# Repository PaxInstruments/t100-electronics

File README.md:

# t100-electronics

### Overview
Pax Instruments T100 thermocouple USB adapter.

## T100 Projects

- [Electronics](https://github.com/PaxInstruments/t100-electronics)
- [Enclosure](https://github.com/PaxInstruments/t100-enclosure)
- [Firmware](https://github.com/PaxInstruments/t100-firmware)
- [Software](https://github.com/PaxInstruments/t100-software)

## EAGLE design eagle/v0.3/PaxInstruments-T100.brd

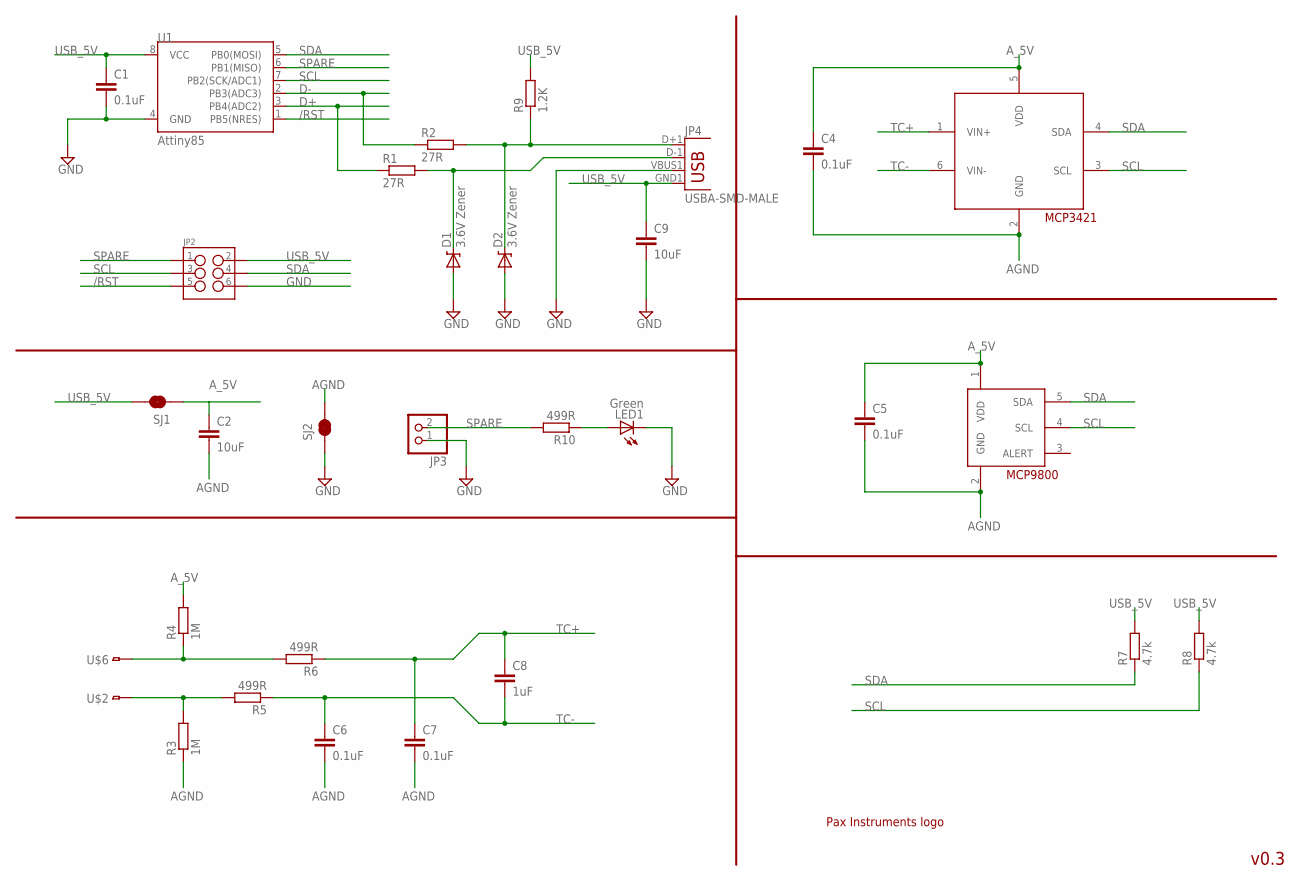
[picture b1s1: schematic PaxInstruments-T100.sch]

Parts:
C1, C4, C5, C6, C7: 0.1uF; C0603; TOLERANCE 5%; MPN CC0603JRX7R9BB104
C2, C9: 10uF; 1206; TOLERANCE 10%; MPN CC1206KKX5R7BB106
C8: 1uF; C0603; TOLERANCE 10%; MPN GRM155R60J105KE19D
D1, D2: 3.6V Zener; SOD-323; MPN BZT52C3V6S-7-F
JP2: M03X2SMT; 2X3_SMT_POSTS; MPN 95278-101A06LF
JP3: HEADER-1X2ROUND; 1X02_ROUND
JP4: USBA-SMD-MALE; USB-A-SMT-MALE
LED1: Green; LED-0603; MPN LTST-C191KGKT
R1, R2: 27R; R0603; TOLERANCE 5%; MPN RC0603JR-0727RL
R3, R4: 1M; R0603; TOLERANCE 1%; MPN RC0603FR-071ML
R5, R6, R10: 499R; R0603; TOLERANCE 0.5%; MPN RT0603DRD07499RL
R7, R8: 4.7k; R0603; TOLERANCE 5%; MPN RC0603JR-074K7L
R9: 1.2K; R0603; TOLERANCE 5%; MPN RC0603JR-071K2L
SJ1, SJ2: JUMPER-PAD-2-NC_BY_TRACENO_SILK; PAD-JUMPER-2-NC_BY_TRACE_NO_SILK
U1: Attiny85; SO08-EIAJ; MPN ATTINY85-20SUR
U$1: PAX-LOGOPAX-LOGO-0.25IN; PAX-LOGO-0.25IN
U$2, U$6: TC-MINI-SINGLE; TC-CLIP-SINGLE; MPN 1024
U$3: MCP3421A0; SOT23-6; MPN MCP3421A0T-E/CH
U$4: MCP9800A0; SOT23-5; MPN MCP9800A0T-M/OT

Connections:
/RST: JP2.5, U1.1 (PB5(NRES))
AGND: C2.2, C4.2, C5.2, C6.2, C7.2, R3.1, SJ2.2, U$3.2 (GND), U$4.2 (GND)
A_5V: C2.1, C4.1, C5.1, R4.2, SJ1.1, U$3.5 (VDD), U$4.1 (VDD)
D+: R1.1, U1.3 (PB4(ADC2))
D-: R2.1, U1.2 (PB3(ADC3))
GND: C1.2, C9.2, D1.2 (A), D2.2 (A), JP2.6, JP3.1, JP4.VBUS1 (VBUS), LED1.C, SJ2.1, U1.4 (GND)
unnamed: D2.1 (C), JP4.D+1 (D+), R2.2, R9.1
unnamed: D1.1 (C), JP4.D-1 (D-), R1.2
unnamed: R3.2, R5.2, U$2.P$1
unnamed: R4.1, R6.2, U$6.P$1
unnamed: LED1.A, R10.1
SCL: JP2.3, R8.1, U1.7 (PB2(SCK/ADC1)), U$3.3 (SCL), U$4.4 (SCL)
SDA: JP2.4, R7.1, U1.5 (PB0(MOSI)), U$3.4 (SDA), U$4.5 (SDA)
SPARE: JP2.1, JP3.2, R10.2, U1.6 (PB1(MISO))
TC+: C7.1, C8.1, R6.1, U$3.1 (VIN+)
TC-: C6.1, C8.2, R5.1, U$3.6 (VIN-)
USB_5V: C1.1, C9.1, JP2.2, JP4.GND1 (GND), R7.2, R8.2, R9.2, SJ1.2, U1.8 (VCC)

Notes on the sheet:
v0.3

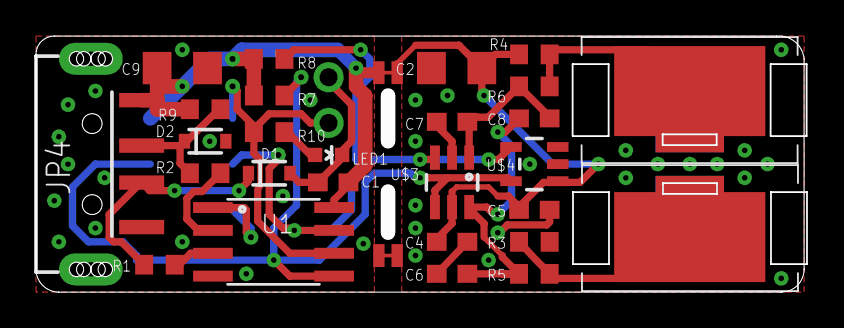
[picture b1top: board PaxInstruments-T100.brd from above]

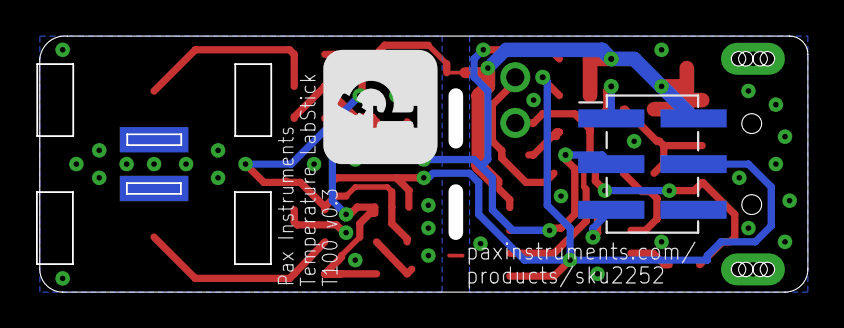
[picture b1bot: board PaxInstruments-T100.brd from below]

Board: 2 copper layers, 42.1 x 13.4 mm, 32 parts (2 on the bottom side), 17 nets.

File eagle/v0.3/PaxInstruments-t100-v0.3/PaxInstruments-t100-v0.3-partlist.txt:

Partlist

Exported from PaxInstruments-T100.sch at 2015-10-05 13:11

EAGLE Version 6.5.0 Copyright (c) 1988-2013 CadSoft

Assembly variant: 

Part     Value          Device                Package        Library                   Sheet

C1       0.1uF          C-EUC0603             C0603          rcl                       1
C2       10uF           CAP1206               1206           SparkFun-Passives         1
C4       0.1uF          C-EUC0603             C0603          rcl                       1
C5       0.1uF          C-EUC0603             C0603          rcl                       1
C6       0.1uF          C-EUC0603             C0603          rcl                       1
C7       0.1uF          C-EUC0603             C0603          rcl                       1
C8       1uF            C-EUC0603             C0603          rcl                       1
C9       10uF           CAP1206               1206           SparkFun-Passives         1
D1       3.6V Zener     DIODE-ZENER-BZT52     SOD-323        SparkFun-DiscreteSemi     1
D2       3.6V Zener     DIODE-ZENER-BZT52     SOD-323        SparkFun-DiscreteSemi     1
JP1      USB-A-H        USB-A-H               USB-A-H        SparkFun-Connectors       1
JP2                     M03X2SMT              2X3_SMT_POSTS  SparkFun-Connectors       1
JP3                     HEADER-1X2ROUND       1X02_ROUND     microbuilder              1
LED1     Green          LED0603               LED-0603       SparkFun-LED              1
R1       27R            R-EU_R0603            R0603          rcl                       1
R2       27R            R-EU_R0603            R0603          rcl                       1
R3       1M             R-EU_R0603            R0603          rcl                       1
R4       1M             R-EU_R0603            R0603          rcl                       1
R5       499R           R-EU_R0603            R0603          rcl                       1
R6       499R           R-EU_R0603            R0603          rcl                       1
R7       4.7k           R-EU_R0603            R0603          rcl                       1
R8       4.7k           R-EU_R0603            R0603          rcl                       1
R9       1.2K           R-EU_R0603            R0603          rcl                       1
R10      499R           R-EU_R0603            R0603          rcl                       1
R11      0R             R-EU_R0603            R0603          rcl                       1
R12      0R             R-EU_R0603            R0603          rcl                       1
U$2      TC-MINI-SINGLE TC-MINI-SINGLE        TC-CLIP-SINGLE PaxInstruments-Connectors 1
U$3      MCP3421A0      MCP3421               SOT23-6        SparkFun-DigitalIC        1
U$4      MCP9800A0      MCP9800               SOT23-5        SparkFun-DigitalIC        1
U$6      TC-MINI-SINGLE TC-MINI-SINGLE        TC-CLIP-SINGLE PaxInstruments-Connectors 1
U1       Attiny85       ATTINY45TINY45-20-SMT SO08-EIAJ      SparkFun-DigitalIC_ihsan  1

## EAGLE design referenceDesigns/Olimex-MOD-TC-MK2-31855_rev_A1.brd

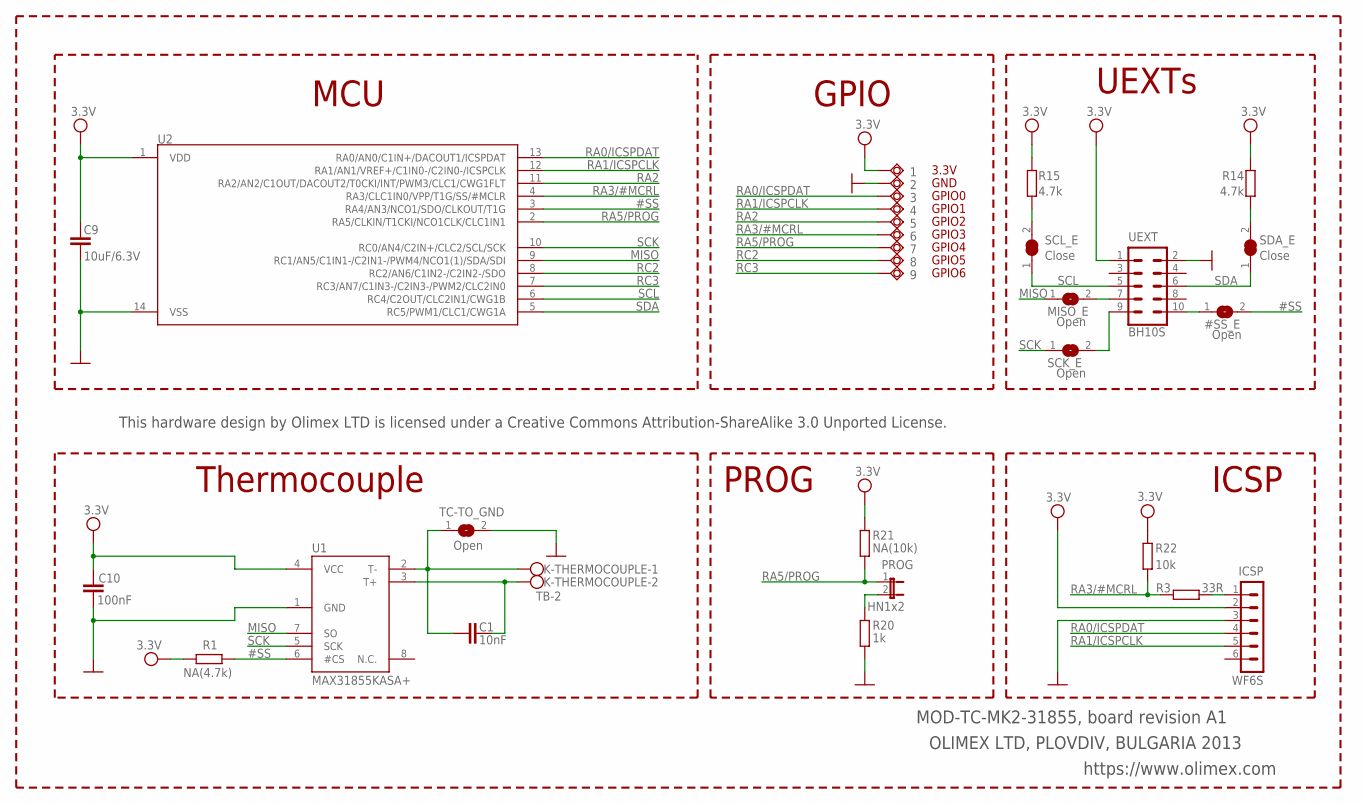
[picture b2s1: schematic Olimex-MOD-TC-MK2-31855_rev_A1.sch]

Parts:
1, 2, 3, 4, 5, 6, 7, 8, 9: TESTPAD40/70; TESTPAD
#SS_E: Open; SJ_1_SMALLER
C1: 10nF; C0603_5MIL
C9: 10uF/6.3V; C0603_5MIL
C10: 100nF; C0603_5MIL
ICSP: WF6S
K-THERMOCOUPLE: TB-2; AK500/2
MISO_E: Open; SJ_1_SMALLER
PROG: HN1x2; JP1
R1: NA(4.7k); R0603_5MIL
R3: 33R; R0603_5MIL
R14, R15: 4.7k; R0603_5MIL
R20: 1k; R0603_5MIL
R21: NA(10k); R0603_5MIL
R22: 10k; R0603_5MIL
SCK_E: Open; SJ_1_SMALLER
SCL_E: Close; SJ_1_SMALLER_CLOSE
SDA_E: Close; SJ_1_SMALLER_CLOSE
TC-TO_GND: Open; SJ_1_SMALLER
U1: MAX31855KASA+; SO-08
U2: PIC16F1503-I/SL; SOIC14
UEXT: BH10S; ML10_PADS

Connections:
#SS: #SS_E.2, R1.2, U1.6 (#CS), U2.3 (RA4/AN3/NCO1/SDO/CLKOUT/T1G)
GND: 2.P$1, C9.2, C10.2, ICSP.3, R20.1, TC-TO_GND.2, U1.1 (GND), U2.14 (VSS), UEXT.2
MISO: MISO_E.1, U1.7 (SO), U2.9 (RC1/AN5/C1IN1-/C2IN1-/PWM4/NCO1(1)/SDA/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)
unnamed: #SS_E.1, UEXT.10
unnamed: SCK_E.2, UEXT.9
unnamed: MISO_E.2, UEXT.7
unnamed: C1.1, K-THERMOCOUPLE.1, TC-TO_GND.1, U1.2 (T-)
unnamed: C1.2, K-THERMOCOUPLE.2, U1.3 (T+)
unnamed: ICSP.1, R3.1
unnamed: R14.1, SDA_E.2
unnamed: R15.1, SCL_E.2
unnamed: PROG.2, R20.2
RA0/ICSPDAT: 3.P$1, ICSP.4, U2.13 (RA0/AN0/C1IN+/DACOUT1/ICSPDAT)
RA1/ICSPCLK: 4.P$1, ICSP.5, U2.12 (RA1/AN1/VREF+/C1IN0-/C2IN0-/ICSPCLK)
RA2: 5.P$1, U2.11 (RA2/AN2/C1OUT/DACOUT2/T0CKI/INT/PWM3/CL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)
RA3/#MCRL: 6.P$1, R3.2, R22.2, U2.4 (RA3/CLC1IN0/VPP/T1G/SS/#MCLR)
RA5/PROG: 7.P$1, PROG.1, R21.1, U2.2 (RA5/CLKIN/T1CKI/NCO1CLK/CLC1IN1)
RC2: 8.P$1, U2.8 (RC2/AN6/C1IN2-/C2IN2-/SDO)
RC3: 9.P$1, U2.7 (RC3/AN7/C1IN3-/C2IN3-/PWM2/CLC2IN0)
SCK: SCK_E.1, U1.5 (SCK), U2.10 (RC0/AN4/C2IN+/CLC2/SCL/SCK)
SCL: SCL_E.1, U2.6 (RC4/C2OUT/CLC2IN1/CWG1B), UEXT.5
SDA: SDA_E.1, U2.5 (RC5/PWM1/CLC1/CWG1A), UEXT.6
VCC: 1.P$1, C9.1, C10.1, ICSP.2, R1.1, R14.2, R15.2, R21.2, R22.1, U1.4 (VCC), U2.1 (VDD), UEXT.1

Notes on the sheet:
ICSP
MCU
UEXTs
Thermocouple
GPIO4
GPIO5
GPIO6
GPIO1
GPIO2
GPIO3
GPIO0
GND
3.3V
GPIO
PROG
MOD-TC-MK2-31855, board revision A1
OLIMEX LTD, PLOVDIV, BULGARIA 2013
https://www.olimex.com
This hardware design by Olimex LTD is licensed under a Creative Commons Attribution-ShareAlike 3.0 Unported License.

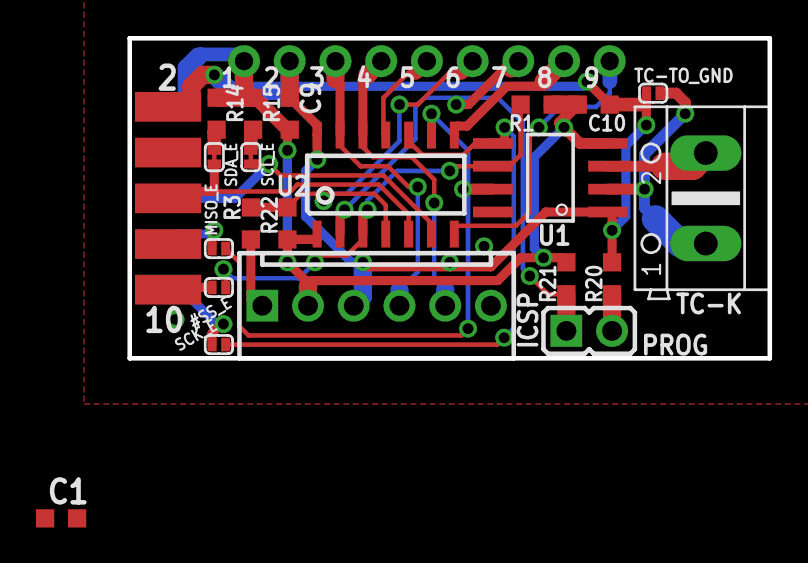
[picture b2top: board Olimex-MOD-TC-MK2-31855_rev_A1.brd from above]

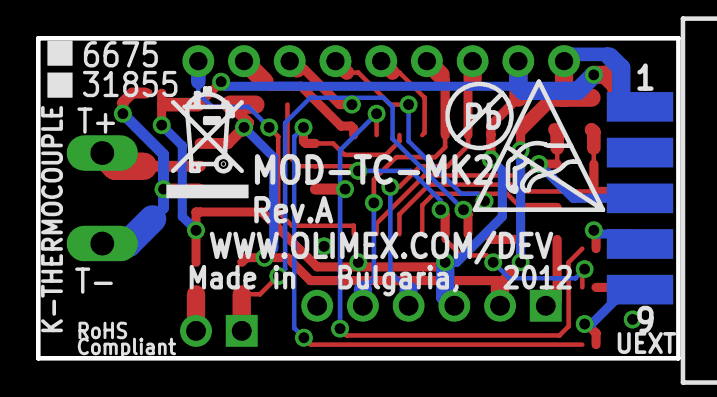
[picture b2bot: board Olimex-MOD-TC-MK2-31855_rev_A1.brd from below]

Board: 2 copper layers, 35.6 x 17.8 mm, 34 parts (4 on the bottom side), 23 nets.

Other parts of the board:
U$1: ESD_SYMBOL
U$6: RECYCLE_BIN1/8
U$7: PB_SMALL

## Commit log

2014-09-16 - added Olimex-MOD-TC-MK2 to referenceDesigns
2014-09-16 - Added SerialCouple to referenceDesigns
2014-09-16 - Added GGLab us tk01 to referenceDesigns
2014-09-16 - Removed spec sheet information. All info is in Github issues
2014-09-21 Initial firmware commit with minimum viable functionality.
2014-09-21 Buffer index fix.
2014-09-22 Firmware is moved to its proper place
2014-10-01 - Added Digispark reference designs - Added USB-to-thermocouple data sheet
2014-10-12 Initial schematic and mockup layout commit.
2014-10-13 ISP connector is modified.
2014-10-13 Layout changes with thermal cutout
2014-10-16 - Changed .gitignore.
2014-11-12 Add fab check files
2014-11-12 Fixed clearance issues, added round corners and version number to the layout
2014-11-28 - Added an order form. This is what Charles uses in China.
2014-11-28 updated .gitignore
    - Ignoring .gpi files
    - Ignoring .dri files
2015-01-01 new file: libraries/PaxInstrument-T400.lbr
2015-01-01 TC connector is updated with the current one. Missing USB pullup resistor added
2015-01-01 modified: libraries/SparkFun-DigitalIC.lbr modified: libraries/charlespax.lbr
2015-01-01 Date code and version number updated
2015-01-02 - Added dottiest
2015-02-23 Initial v0.3 design with isothermal plane connection changed to solder jumper.
2015-02-23 Added indicator LED and breakout header.
2015-02-23 new file: libraries/microbuilder.lbr
2015-08-24 [V0.3] - initial layout
2015-08-24 deleted: eagle/.DS_Store
2015-08-25 New library added. Inductor changed to resistor. Logo placement.
2015-08-25 Text label placements.
2015-09-25 Added MCP9800A0 part number. Closes #47.
2015-09-25 Added a bunch of BoM data.
2015-09-25 Updated thermocoupel connector. Moved MCP9800 to between the thermocouple connectors. BoM should be finished.
2015-09-26 Updated thermocouple connector with th emost recent version.
2015-10-05 Made via holes smaller. Verified design. Ready to order PCBs. Added 0.3 fab files.
2015-12-27 Changed USB connector. Updated thermocouple footprint. Rerouted board.
2015-12-31 Ordering new 0.3 files.
2016-01-03 Added fabrication files to v3.
2016-01-05 Moved component names on PCB. Added location PDF.

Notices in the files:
parts and their libraries:
SparkFun-DigitalIC_ihsan: Licensing: CC v3.0 Share-Alike You are welcome to use this library for commercial purposes.
microbuilder: This work is placed in the public domain, and may be freely used for commercial and non-commercial work with the following conditions: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
